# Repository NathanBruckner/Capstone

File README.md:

**FTS RAIL CAPSTONE**

This repository contains all code and notes pertaining to the FTS Railroad Gauge Spreader Capstone Project.

Primary Contributor: _Nathan Bruckner_
Last Updated: _09/17/2025_

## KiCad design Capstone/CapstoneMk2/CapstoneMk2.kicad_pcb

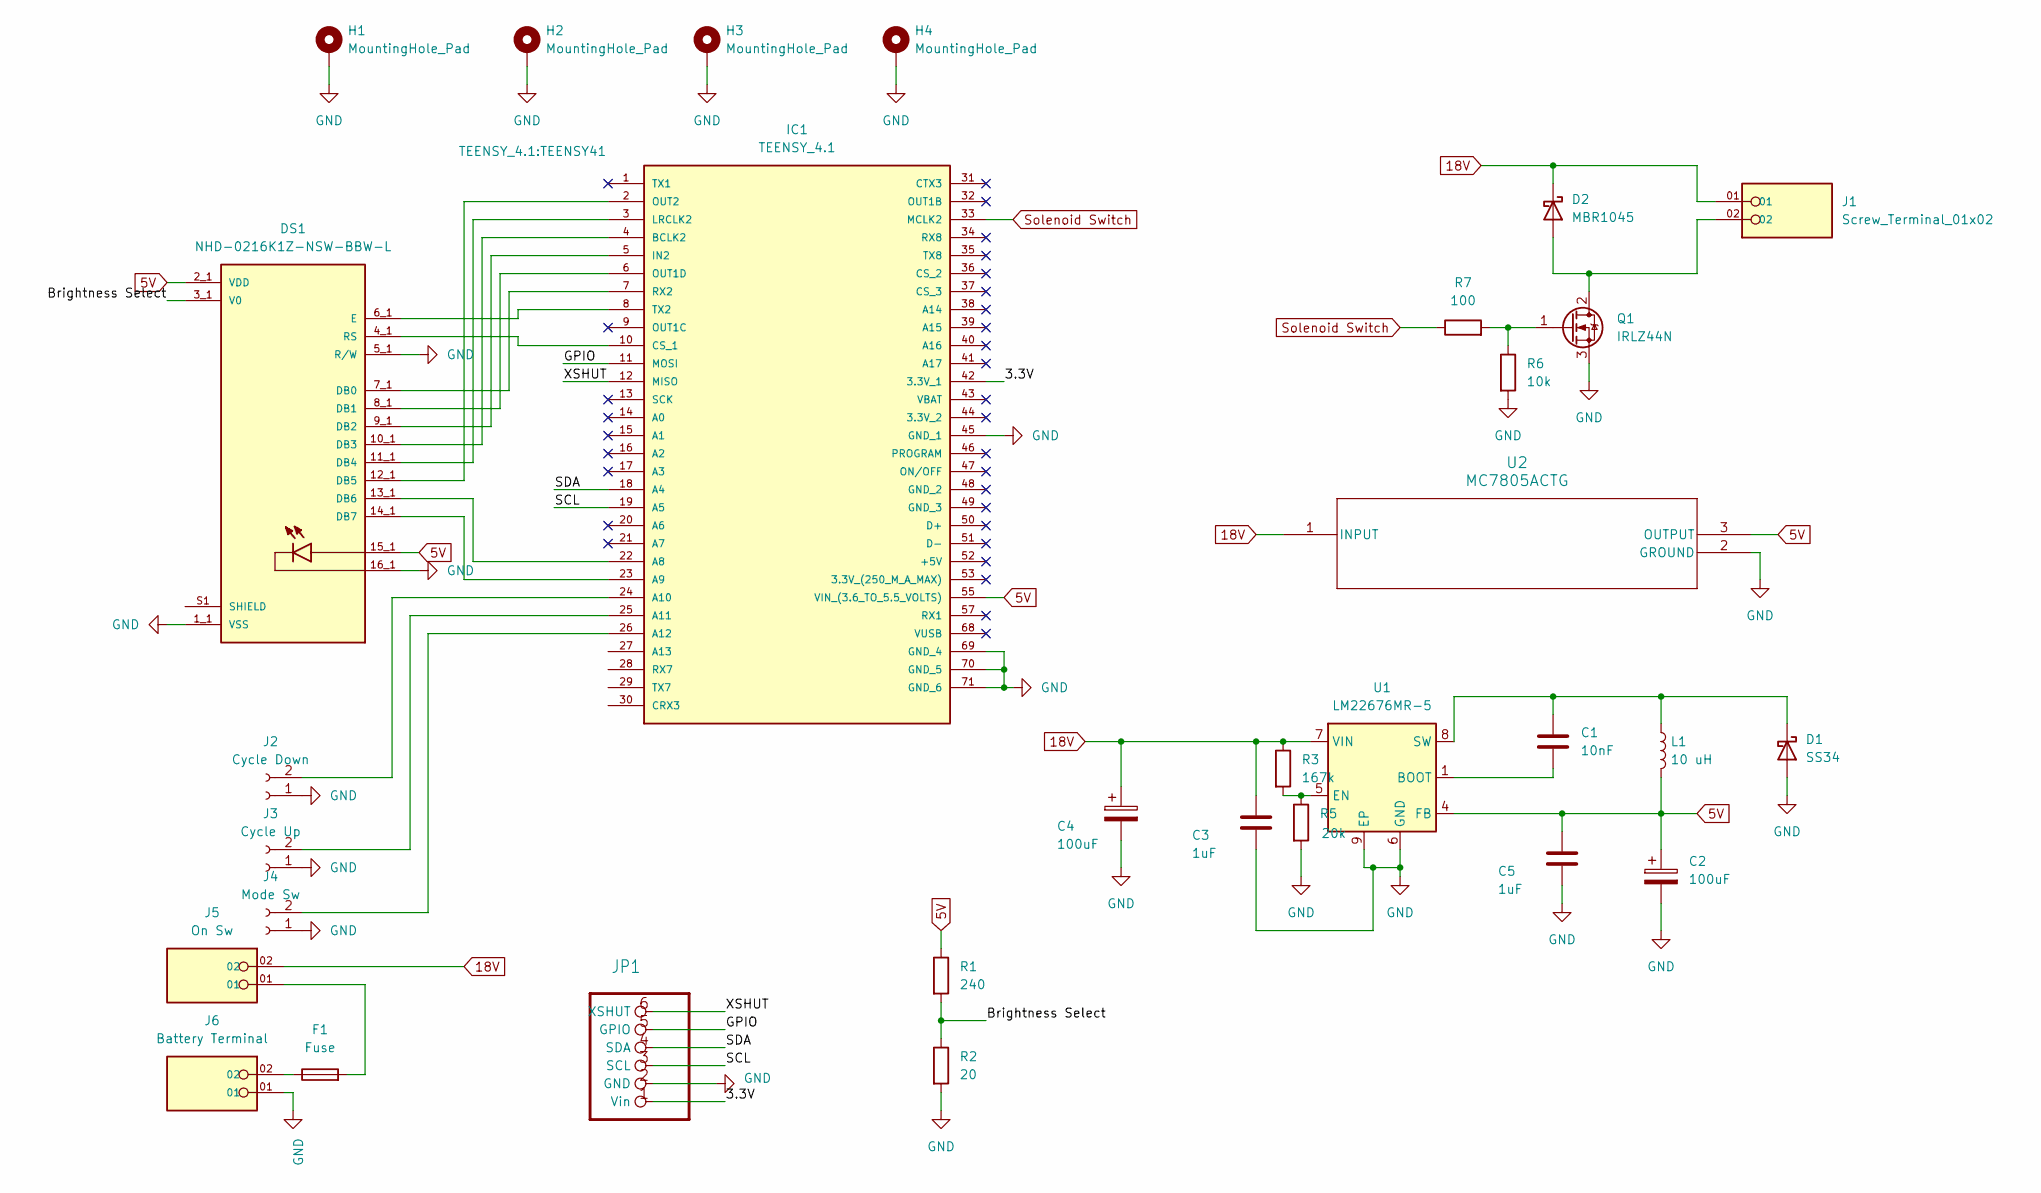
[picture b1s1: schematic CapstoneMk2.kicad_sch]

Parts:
C1: 10nF; C_0402_1005Metric_Pad0.74x0.62mm_HandSolder
C2: 100uF; CP_Radial_D5.0mm_P2.00mm
C3, C5: 1uF; C_0805_2012Metric_Pad1.18x1.45mm_HandSolder
C4: 100uF; CP_Radial_D8.0mm_P3.50mm
D1: SS34; D_SMA
D2: MBR1045; TO-220-2_Vertical
DS1: NHD-0216K1Z-NSW-BBW-L; NHD_NHD-0216K1Z-NSW-BBW-L; PARTREV 03/28/17
F1: Fuse; Fuse_1206_3216Metric
H1, H2, H3, H4: MountingHole_Pad; MountingHole_3.2mm_M3_Pad_Via
IC1: TEENSY_4.1; TEENSY41; Manufacturer_Part_Number TEENSY 4.1
J1: Screw_Terminal_01x02; PHOENIX_1985807; PARTREV 03.03.2021; DigiKey_Part_Number 277-6043-ND
J2: Cycle Down; JST_XH_S2B-XH-A_1x02_P2.50mm_Horizontal
J3: Cycle Up; JST_XH_S2B-XH-A_1x02_P2.50mm_Horizontal
J4: Mode Sw; JST_XH_S2B-XH-A_1x02_P2.50mm_Horizontal
J5: On Sw; PHOENIX_1985807; PARTREV 03.03.2021; DigiKey_Part_Number 277-6043-ND
J6: Battery Terminal; PHOENIX_1985807; PARTREV 03.03.2021; DigiKey_Part_Number 277-6043-ND
JP1: JST_XH_S6B-XH-A_1x06_P2.50mm_Horizontal
L1: 10 uH; INDPM7870X320N
Q1: IRLZ44N; TO-220-3_Vertical
R1: 240; R_1206_3216Metric
R2: 20; R_1206_3216Metric
R3: 167k; R_0603_1608Metric
R5: 20k; R_0603_1608Metric
R6: 10k; R_0402_1005Metric_Pad0.72x0.64mm_HandSolder
R7: 100; R_0402_1005Metric_Pad0.72x0.64mm_HandSolder
U1: LM22676MR-5; TI_SO-PowerPAD-8
U2: MC7805ACTG

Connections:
5V: C2.1, C5.1, DS1.2_1 (VDD), DS1.2_2 (VDD), DS1.15_1, DS1.15_2, IC1.55 (VIN_(3.6_TO_5.5_VOLTS)), L1.2, R1.1, U1.4 (FB), U2.3 (OUTPUT)
18V: C3.1, C4.1, D2.1 (K), J1.01, J5.02, R3.1, U1.7 (VIN), U2.1 (INPUT)
/3.3V: IC1.42 (3.3V_1), JP1.1 (Vin)
/GPIO: IC1.11 (MOSI), JP1.5 (GPIO)
/SCL: IC1.19 (A5), JP1.3 (SCL)
/SDA: IC1.18 (A4), JP1.4 (SDA)
/XSHUT: IC1.12 (MISO), JP1.6 (XSHUT)
GND: C2.2, C3.2, C4.2, C5.2, D1.2 (A), DS1.1_1 (VSS), DS1.1_2 (VSS), DS1.5_1 (R/W), DS1.5_2 (R/W), DS1.16_1, DS1.16_2, H1.1, H2.1, H3.1, H4.1, IC1.45 (GND_1), IC1.69 (GND_4), IC1.70 (GND_5), IC1.71 (GND_6), J2.1, J3.1, J4.1, J6.01, JP1.2 (GND), Q1.3 (S), R2.2, R5.2, R6.2, U1.6 (GND), U1.9 (EP), U2.2 (GROUND)
unnamed: C1.1, D1.1 (K), L1.1, U1.8 (SW)
unnamed: D2.2 (A), J1.02, Q1.2 (D)
unnamed: DS1.S1 (SHIELD), DS1.S2 (SHIELD), DS1.S3 (SHIELD), DS1.S4 (SHIELD)
unnamed: F1.1, J6.02
unnamed: F1.2, J5.01
unnamed: DS1.13_1 (DB6), DS1.13_2 (DB6), IC1.22 (A8)
unnamed: DS1.14_1 (DB7), DS1.14_2 (DB7), IC1.23 (A9)
unnamed: IC1.24 (A10), J2.2
unnamed: IC1.25 (A11), J3.2
unnamed: IC1.26 (A12), J4.2
unnamed: DS1.10_1 (DB3), DS1.10_2 (DB3), IC1.4 (BCLK2)
unnamed: DS1.4_1 (RS), DS1.4_2 (RS), IC1.10 (CS_1)
unnamed: DS1.9_1 (DB2), DS1.9_2 (DB2), IC1.5 (IN2)
unnamed: DS1.11_1 (DB4), DS1.11_2 (DB4), IC1.3 (LRCLK2)
unnamed: DS1.8_1 (DB1), DS1.8_2 (DB1), IC1.6 (OUT1D)
unnamed: DS1.12_1 (DB5), DS1.12_2 (DB5), IC1.2 (OUT2)
unnamed: DS1.7_1 (DB0), DS1.7_2 (DB0), IC1.7 (RX2)
unnamed: DS1.6_1 (E), DS1.6_2 (E), IC1.8 (TX2)
unnamed: Q1.1 (G), R6.1, R7.2
unnamed: C1.2, U1.1 (BOOT)
unnamed: R3.2, R5.1, U1.5 (EN)
Solenoid Switch: IC1.33 (MCLK2), R7.1
V0: DS1.3_1 (V0), DS1.3_2 (V0), R1.2, R2.1

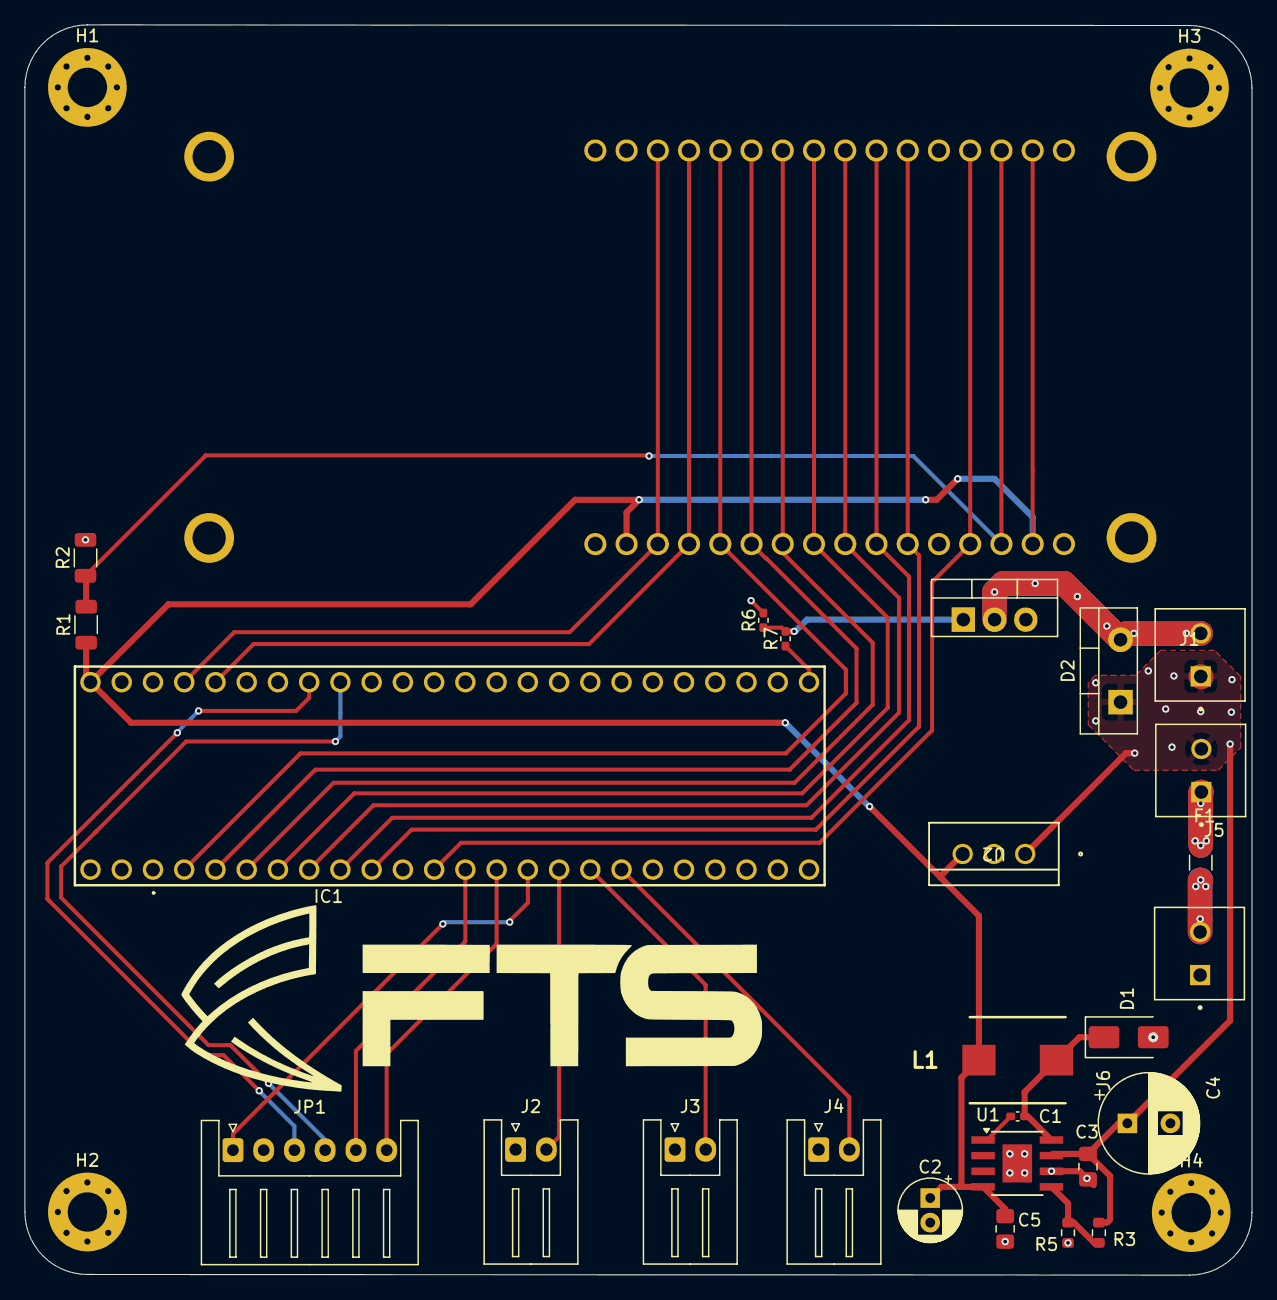
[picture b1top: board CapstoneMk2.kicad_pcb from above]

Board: 2 copper layers, 99.8 x 101.7 mm, 31 parts (1 on the bottom side), 31 nets.

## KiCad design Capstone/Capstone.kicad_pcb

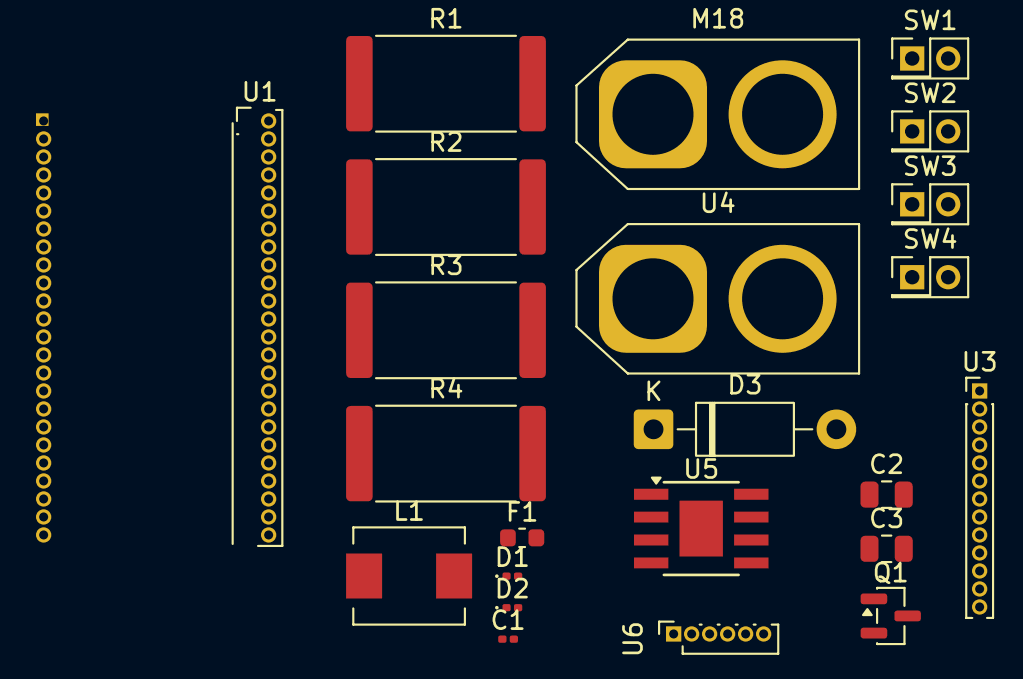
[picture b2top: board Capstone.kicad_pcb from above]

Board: 2 copper layers, 23 parts (0 on the bottom side), 20 nets, no tracks yet.

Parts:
C1: 10 nF; C_0201_0603Metric
C2: 120 uF; C_0805_2012Metric
C3: 0.1 uF; C_0805_2012Metric
D1, D2: D_Schottky; D_0201_0603Metric
D3: 1N4007; D_DO-41_SOD81_P10.16mm_Horizontal
F1: 10A Fuse; Fuse_0603_1608Metric
L1: 50.8 uH; L_Neosid_SM-PIC0512H
M18: Battery; AMASS_XT60-F_1x02_P7.20mm_Vertical
Q1: Si2319CDS; SOT-23
R1: 4.7k Ohm; R_4020_10251Metric
R2: 24 kOhm; R_4020_10251Metric
R3: 69.4 kOhm; R_4020_10251Metric
R4: 0 kOhm; R_4020_10251Metric
SW1: On/Off Switch; PinHeader_2x01_P2.00mm_Vertical
SW2: Cycle Up; PinHeader_2x01_P2.00mm_Vertical
SW3: Cycle Down; PinHeader_2x01_P2.00mm_Vertical
SW4: Auto / Manual; PinHeader_2x01_P2.00mm_Vertical
U1: Teensy4.1; PinHeader_2x24_P1.00mm_Vertical
U3: PinHeader_1x13_P1.00mm_Vertical
U4: AMASS_XT60-F_1x02_P7.20mm_Vertical
U5: LM22676MR-5; TI_SO-PowerPAD-8
U6: PinSocket_1x06_P1.00mm_Vertical

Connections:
GND: C2.1, C3.2, D1.2 (A), D2.2 (A), L1.1, M18.2 (-), Q1.3 (D), R1.2, R2.2, SW2.2, SW3.2, SW4.1, U1.1 (GND), U1.47 (GND), U3.2 (VDD), U3.3 (V0), U5.6 (GND)
unnamed: C3.1, D1.1 (K), D3.1 (K), F1.2, SW1.1
unnamed: C1.2, D2.1 (K), U5.1 (BOOT)
unnamed: D3.2 (A), Q1.2 (S)
unnamed: F1.1, M18.1 (+)
unnamed: Q1.1 (G), R1.1, R4.2
unnamed: SW4.2, U1.2 (0_RX1_CRX2_CS1)
unnamed: SW3.1, U1.3 (1_TX1_CTX2_MISO1)
unnamed: R4.1, U1.4 (2_OUT2)
unnamed: SW2.1, U1.5 (3_LRCLK2)
unnamed: U1.7 (5_IN2), U3.13 (DB6)
unnamed: U1.8 (6_OUT1D), U3.12 (DB5)
unnamed: C2.2, L1.2, R3.2, U1.9 (7_RX2_OUT1A), U1.48 (VIN), U3.1 (VS), U3.11 (DB4)
unnamed: U1.10 (8_TX2_IN1), U3.10 (DB3)
unnamed: U1.11 (9_OUT1C), U3.9 (DB2)
unnamed: U1.12 (10_CS_MQSR), U3.8 (DB1)
unnamed: U1.13 (11_MOSI_CTX1), U3.7 (DB0)
unnamed: R2.1, R3.1, U5.4 (FB)
unnamed: C1.1, U5.8 (SW)
unnamed: SW1.2, U5.7 (VIN)

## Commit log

2025-09-17 Meeting notes 09/17/2025; Updated readme;
2025-09-17 updated notes
2025-09-17 Organization
2025-09-17 Added Mechanical bologna
2026-01-21 Added some kicad files and the startup sketch for the teensy
2026-04-30 Working measurement. Unexpected freezing occurs. Commit prior to testing the clutch engagement with measurement system
